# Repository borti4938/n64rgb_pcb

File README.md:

N64RGBv2.1 (PCB)
---

This repository contains all you need files to build your own DIY N64RGBv2.1 board.
Firmware is supplied in another repository.

Please don't ask me for selling a modding.
I either sell some prototypes on some forums marketplaces (which is very unlikely) or I don't have any of the boards.
This is a complete DIY modding project.
Everybody is on his own here.

**WARNING:**
This is an advanced DIY project if you do everything on your own. You need decent soldering skills.
The CPLD and the video DAC have 0.5mm fine pitched pins.
On the board there are some SMD1206 resistor and ferrite bead arrays.
However, there are some awesome shops out there selling the boards for a great price.

## Table of Contents

- [Checklist](https://github.com/borti4938/n64rgb_pcb#checklist-how-to-build-the-project)
- [Assembly](https://github.com/borti4938/n64rgb_pcb#assembly)
- [Installation](https://github.com/borti4938/n64rgb_pcb#installation)
  - [1. Open the Console](https://github.com/borti4938/n64rgb_pcb#1-open-the-console)
  - [2. Optional Steps](https://github.com/borti4938/n64rgb_pcb#2-optional-steps)
  - [3. Solder Work](https://github.com/borti4938/n64rgb_pcb#3-solder-work)
  - [4. Mount the N64 Advanced Modding PCB](https://github.com/borti4938/n64rgb_pcb#4-mount-the-n64-advanced-modding-pcb)
  - [5. Finish the Work](https://github.com/borti4938/n64rgb_pcb#5-finish-the-work)
- [Jumper Setup](https://github.com/borti4938/n64rgb_pcb#jumper-setup)
- [Cable Setup](https://github.com/borti4938/n64rgb_pcb#cable-setup)

## Checklist: How to build the project

- Use PCB files (either [KiCad-PCB design file](./n64rgbv2.1.kicad_pcb) or [Gerber files](./Gerber/)) to order your own PCB or simply use the [shared project(s) on OSHPark](https://oshpark.com/profiles/borti4938)
- If you paln to use solder paste, do not forget to order a stencil for top and bottom, too
- Source the components you need, e.g. from Mouser or Digikey.  
  The BOM is available in [here](./doc/BOM_n64rgbv2.1.xlsx).
- Wait for everything to arrive
- Assemble your PCB if you haven't use a PCBA service
- Set all jumpers
- Flash the firmware ([firmware releases](https://github.com/borti4938/n64rgb_fw/releases)) to the CPLD after installation (e.g. using an Altera USB Blaster)
  - Use the POF programming file named n64rgbv2\_1\__cpld-device_.pof
  - Using the intelFPGA programmer, JTAG chain is initialized by loading POF file
  - N64 needs to be powered for flashing
  - Power cycle the N64 after flashing
- If you want to go for a clean installation with custom made flexible PCBs, just visit the repository for add ons ([Flex PCB for the digital video interface](https://github.com/borti4938/n64rgb_project_misc/RCP2N64RGB), [Flex PCB for the analog video output](https://github.com/borti4938/n64rgb_project_misc/N64RGB2MoutFilter)

## Assembly

If you have all components available, you can start assembly your board.
The documentation provides assembly sheets ([top](./doc/n64rgb2.1_assembly_sheet_top.pdf) and [bottom](./doc/1_assembly_sheet_bot.pdf), which you can print out.
Together with the [BOM](./doc/BOM_n64rgbv2.1.xlsx) it is just a matter of time and effort to assembly everything.
Alternatively you can also use the [interactive BOM](./doc/ibom.html).

Please note that the assembly (and component sourcing) depends on which kind of CPLD family you use.
Supported are Max II and Max V CLPDs.
- If you use a Max II CPLD, you must use FB3 and leave U4, C41 and C42 unpopulated.
- If you use a Max V CPLD, you must use U4, C41 and C42 and leave FB3 unpopulated.

If you populate J3, which is the JTAG connector, please short the pins such that they are flush at the bottom side.
This reduces the risk to short on of these pins with the heat sink (where the PCB will be mounted).

Using non-clean flux (rosin based) is obviously recommended.
Even though it is "non-clean" I recommend cleaning everything afterwards (just for the visual finish).

Please double check everything for shorts once you finished your work.
Very important is that the power supply trace do not short to GND.
- 3.3V against GND (e.g. at C1 and at C52)
- 1.8V against GND (e.g. at C42)
- 5V against GND (e.g. at C4)

## Installation

Note that installation pictures partially show the N64Advanced board.
Pad design and installation is equivalent.

### 1. Open the console

- Remove Jumper Pak / Expansion Pak
- Remove screws from bottom side of the console  
(needs a 4.5mm gamebit tool)
- Lift top housing
- remove inner screws as marked  
(very last consoles made the heat sink design changed slightly)
- pull out the mainboard
- remove heat sink and RF shield
- **Hint** Now you have the chance to clean up your N64 shell

(image by Zerberus (circuit-board.de user))

### 2. Optional Steps

#### 2.1 Preparation of Top RF Shield

This step is optional.
It helps a) to reduce mechanical stress on the flex cable (if used) and b) ensures maximal distance between digital signals (installation wires or flex cable) and analog signals (MultiOut).

- Locate the tap in the RF shield next to the cartridge slot at the side of the MultiOut.  
(this is the place where the installation wires / flex cable will be routed through)
- option 1: bend the tap away

- option 2: simply cut the tab incl. the small piece up to the step in the RF shield

##### Some explanation on this optional step

Later, the data lines as well as the clock will be routed close to the MultiOut.
The distance between both is a crucial issue as your wires act as interferer.
Hence, having the tap bended might be ok, but it is better to cut some piece of the RF shield away to further increase the distance between MultiOut and data lines

#### GND insulation on the MultiOut

To have a better return path for the digital video lines defined, you may insulate GND from the MultiOut.
This step is only recommended if you have a noisy picture.
It comes with the drawback that a) you have a lot of more effort during installation and b) having a longer return path for the analog audio output as well as for S-Video and Composite Video as GND is later routed over the modding board.

- de-solder the MultiOut connector
- drill out the GND pads
- insulare the drills (e.g. with varnish (flex cable or wire install) or small shrink tubes (only wire installation))
- solder MultiOut back into place

### 3. Solder Work

You have the options to either install everything with casual installation wires or using flex cables.
This is just a trade-off between personal installation effort and price.
Personally, I recommend using the flex cable.

Sections 3.1 and 3.2 assume that you want to use the controller functions, so controller 1 will be connected.
However, this is optional, yet at the flex install the controller pad of the flex cable must not be left open!
Please also note section 3.3, where the installation of mechanical switches is described.

#### 3.1 Using the Flex Cable 

To use this option, you have to have the flex cables as shown at hand.
Note that the picture shows older prototype version.

##### 3.1.1 Digital inputs

Start with the digital side:
- Solder the RCP connector side to the RCP-NUS as shown
  - first pin bottom – 8
  - last pin to – 28
- Connect 3.3V to the flex, e.g. taken from C141
- Connect Ctrl. and reset
  - reset from PIF-NUS pin 27
  - Controller from PIF-NUS pin 16  
  (Make sure that PIF-NUS pin 16 is connected to the middle pin of controller port 1, otherwise search for a suitable connection point)
- bend the flex as marked in a way such that you do not see the shaded area anymore.  
The flex will be routed over the MultiOut.

**Note**: when using the flex of version earlier than _v2022xxyy_ you need to cut the RF shield near the MultiOut as shown in 2.1

##### 3.1.2 Analog outputs

Next up is the analog video flex which will be connected to the MultiOut.
Before you start here, make yourself clear where you want to route sync to.
This depends on whether you want to use sync on luma or sync on composite sync (raw sync) cable.

- Free the sync pin from the MultiOut, which means that you must trace back the copper track from the MultiOut pin and make sure that there is nothing connected to.
  - pin 3 (raw sync cable): usually unconnected. Only connected in earlier NTSC console (-CPU-01 to -CPU-03)
  - pin 7 (luma sync cable): usually connected. Search for a nearby resistor or trace back to the DENC-NUS or MAV-NUS and lift the luma pin. Remove the resistor or lift the pin at the DENC-NUS or MAV-NUS.
- solder the flex on its place of the MultiOut
- close **SJ1** on the flex from
  - middle to 3 if using raw sync
  - middle to 7 if using luma sync
- Note that it is also possible to connect sync pin 9 if you want to use a sync on composite video cable.
  - disconnect composite vide from pin 9 using the back tracing technique
  - solder a small wire from **SJ1** middle pad to pin 9 of the MultiOut

#### 3.2 Using Wires

First you need to work out the digital video signals as well as reset and controller 1. 
Most of the signals needed has to be taken from video processor output; the RCP-NUS.
Next to the RCP-NUS is the video encoder, where several types are used during the variety of N64 designs.
The pinouts are given below.
Basically, we need D0-D6, /DSYNC and /CLK (or VCLK or CLOCK) for the modding board.

(RCP-NUS picture by Marshall; Encoder picture by Viletim)

Next to the video signals, you will need to get power (3.3V and GND), reset and controller 1.
This means you need in total 13 wires.
If you use a ribbon cable, I recommend you to use either a 15 conductor cable (double 3.3V and GND) or a 11 conductor cable and separate 3.3V and GND wires. 

- Locate the video encoder
  - Solder a bunch of wires to the video signal pins D0-D6, /DSYNC and /CLK
- Solder wires for reset and controller 1
  - reset from PIF-NUS pin 27
  - Controller from PIF-NUS pin 16  
  (Make sure that PIF-NUS pin 16 is connected to the middle pin of controller port 1, otherwise search for a suitable connection point)
- Solder two additional wires for 3.3V (can be picked off C141) and one for GND (large GND plane)
- Route all wires to the MultiOut port

Next you can prepare wires for the analog video.
Connect several wires to the MultiOut.
Before you start here, make yourself clear where you want to route sync to.
This depends on whether you want to use a sync on composite video, a sync on luma or a sync on composite sync (raw sync) cable.

- Free the sync pin from the MultiOut, which means that you have to trace back the copper track from the MultiOut pin and make sure that there is nothing connected to.
  - pin 3 (raw sync cable): usually unconnected. Only connected in earlier NTSC console (-CPU-01 to -CPU-03)
  - pin 7 (luma sync cable): usually connected. Search for a nearby resistor or trace back to the DENC-NUS or MAV-NUS and lift the luma pin. Remove the resistor or lift the pin at the DENC-NUS or MAV-NUS.
  - pin 9 (composite video sync cable): usually connected. Search for a nearby resistor or trace back to the DENC-NUS or MAV-NUS and lift the luma pin. Remove the resistor or lift the pin at the DENC-NUS or MAV-NUS.
- Prepare some wires to the following pins
  - pin 1: red
  - pin 2: green
  - pin 4: blue
  - pin 3, 7 or 9: sync
  - pin 5 and/or 6: GND (connect pin 5 **and** pin 6 if you insulated GND from the MultiOut)
  - pin 10: 5V

You have the option to use the [Filter AddOn board](https://github.com/borti4938/n64rgb_project_misc/tree/master/FilterAddOn) here.
Note that the filter is optionally included in on the flex cable setup.

If you use the filter board, you clearly have to solder the filter board first and connect the wire to the pads of the filter board as marked on the silk screen.

#### 3.3 Mechanical switch

You can install mechanical switches to toggle VI-DeBlur on and off and also 16bit mode on and off.
At least I recommend installing a mechanical switch for the VI-DeBlur function.

Source a on/on or on/off switch like [this one](https://etim.net.au/shop/shop.php?crn=209&rn=559&action=show_detail).
If you source the switch as linked you can use [this 3D mount](https://www.thingiverse.com/thing:4584239) for a clean installation.

Connect the switch to J11.1 (VI-DeBlur) and/or to J11.2 (16bit mode) in a way such that the switch leaves the jumper open in one position and closes it at the other position.

### 4. Mount the N64 Advanced Modding PCB

The PCB is designed to fit on the heat sink of the N64.
There is a large via on the PCB where a M3 screw passes through.
Mount the PCB using a M3 screw of length 10mm or 12mm, a set of washers and a nut.
Be careful with the JTAG connector **J3** and ensure that the pins do not short to the heatsink!

If you want to use the heat sink shield as an additional secure GND connection, you can also apply some solder to the mounting via.

If everything is mounted and secured, the PCB should sit like that.

### 5. Finish the Work

Before continuing you can assemble the RF shield and heat sink back to the N64 mainboard.
In that way everything is secured in place where it belongs to.
Of course, if you use an installation with wires, make sure that you know which wire is for what.
On my ealrier installs I used some wire marker.

#### 5.1 With Flex Cable

Bend the flex cables gently at the shaded areas.
In that way you should be able to allign both flex cables at the N64RGBv2.1 modding board.
Solder the flex cables at their places.
(Please note subsection 5.3 - CSYNC).

Connect an extra GND wire as shown in 5.3.

#### 5.2 With Wires

Just connect every wire at its place.
The silk screen shows you where everything goes to.
(Please note subsection 5.3 - CSYNC).
Note that the picture shows an older version of the N64 Advanced.
Newer versions have reset and controller at the left-hand side.

Connect an extra GND wire as shown in 5.4.

#### 5.3 CSYNC

You have the option to connect _/CS_ or _/CS (75ohm)_.
I recommend using _/CS (75ohm)_ except if you have a true TTL sink, which is usually not the case!
In virtually 99% of all setups connecting the sync wire to _/CS (75ohm)_ is the way to go.

On installations with the flex cables follows that you must close SJ3 bottom on the flex.
Please note the Jumper Setup section to correctly setup the sync level.

#### 5.4 Extra GND Wire

Connect an extra GND wire to the heat sink screw.
This improves return path properties of the digital video lines.

## Jumper Setup

Jumpers with three pads have _J1#.1_ and _J1#.2_, where .1 is marked with an _arrow_.
Closing either jumper means that a short to the middle pad is needed.

#### J11 (VI-DeBlur and 16bit mode)

This jumper can act as a power cycle default.
You can also switch the state of the jumper using a mechanical switch to toggle the functions during runtime.

##### J11.1 
- opened: VI-DeBlur off
- closed: VI-DeBlur on

##### J11.2
- opened: 16bit mode off
- closed: 16bit mode on

#### J12 (IGR function control)
##### J12.1 (VI-DeBlur and 16bit mode)
- opened: controller functions for toggle VI-DeBlur and 16bit mode on/off are enabled
- closed: controller functions are disabled

##### J12.2 (in game reset)
- opened: reset by controller enabled
- closed: reset by controller disabled

#### J2 (Filter setup)
Needs filter add on to be installed.

- opened: use low pass filter
- closed: bypass filter

#### J21 (Sync on Green)
- open: SoG disabled
- closed: SoG enabled

#### J31 (CSYNC level @ _/CS (75ohm)_ pad)

- opened: appr. 1.87V @ 75ohm termination, i.e. needs a resistor inside the sync wire further attenuating the signal. Designed to work for cables with 470 ohm resistor inside resulting in appr. 450mV @ 75ohm termination
- closed: appr. 300mV @ 75ohm termination suitable for pass through wired cables at sync, works with standard TV / scaler setup

#### J3
_J3_ is the JTAG connector.

## Cable Setup

| Signal | Pin MultiOut | Pin SCART | Ref. GND in SCART | Cinch Plug | Note |
|:-------|:-------------|:----------|:------------------|:-----------|:-----|
| Red / Pr | 1 | 15 | 13 | Red plug | Using a 220uF cap in series is possible, yet not required |
| Green / Y | 2 | 11 | 9 | Green plug | Using a 220uF cap in series is possible, yet not required |
| Blue / Pb | 4 | 7 | 5 | Blue plug | Using a 220uF cap in series is possible, yet not required |
| Sync | 3, 7 or 9 | 20 | 17 | _not needed_ | Pin: See installation, Cable: see notes below |
| GND | 5, 6 | 4,5,9,13,17,18,21 | | Outer ring of each plug | Pin 21 @ SCART: outer shield |
| +5V | 10 | 16 | 18 | _not needed_ | SCART: use a 180ohm resistor in series |
| Audio left | 11 | 6 | 4 | Red plug | |
| Audio right | 12 | 2 | 4 | White plug | |

#### Notes on Sync:

- I recommend using the 75ohm compatible csync output.  
  You have a modding board with J31, you can select with J31 whether
  - you have a series resistor in you cable (J31 open) or
  - if you have a straightly wired sync connection (J31 closed).
- If you use TTL sync output, you have to add an additional resistor in series in every case if you want to use the cable on a non-TTL setup (0ohm to 900ohm) to attenuate the signal for  sinks with 75ohm.

#### RGB cables:

- If you buy an RGB cable, buy a typical RGB cable for a NTSC SNES with sync on luma (MultiAV pin 7) or sync on csync (MultiAV pin 3).
- If you bought a raw csync cable and if you use the 75ohm output, please ensure to set J31 correctly
  
#### PAL RGB cables (SNES PAL):

- PAL RGB cable, i.e. a cable with additional 75ohm resistors to GND, are not supported out of the box.
- You can support them if and only if you have the _Filter AddOn_.  
  To support the cable, replace RN2 with a 39ohm resistor array or solder a second 75ohm resistor array on top of the existing one.

#### RGsB Cables (Cinch):

With the given table you should be able to build your own component cable (passing RGB) or to build an adapter (see pictures below)
Unfortunately, there are no cables / adapter to buy.
Only chance is to buy a Wii component cable and use a MultiOut adapter (SNES/N64/GC style to Wii style).

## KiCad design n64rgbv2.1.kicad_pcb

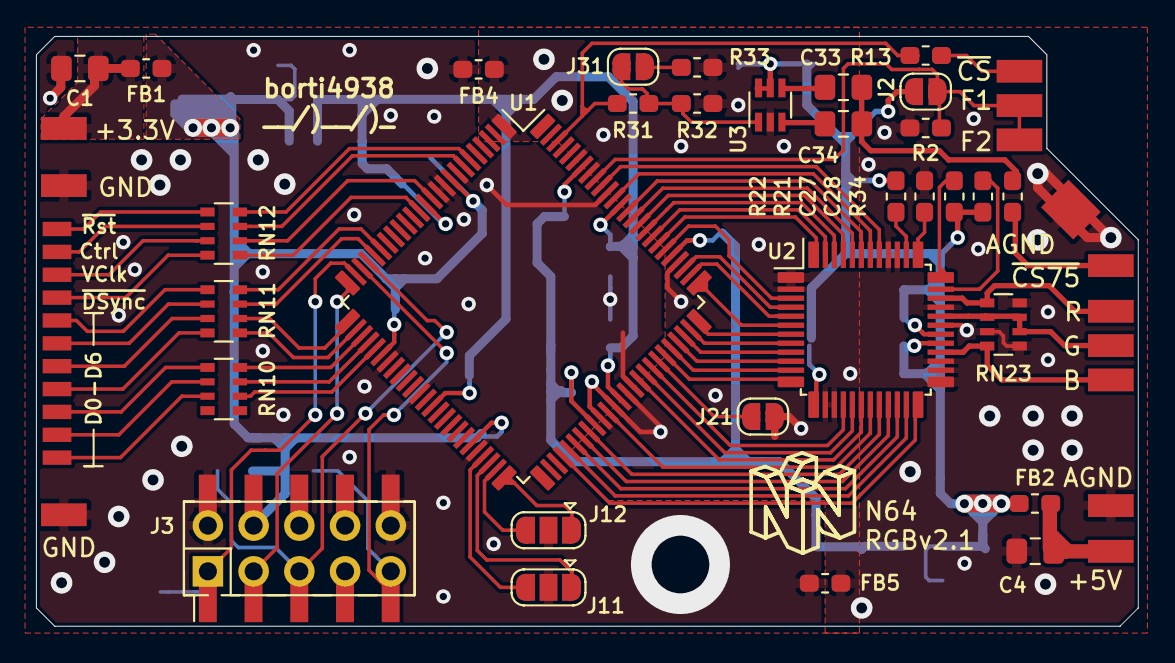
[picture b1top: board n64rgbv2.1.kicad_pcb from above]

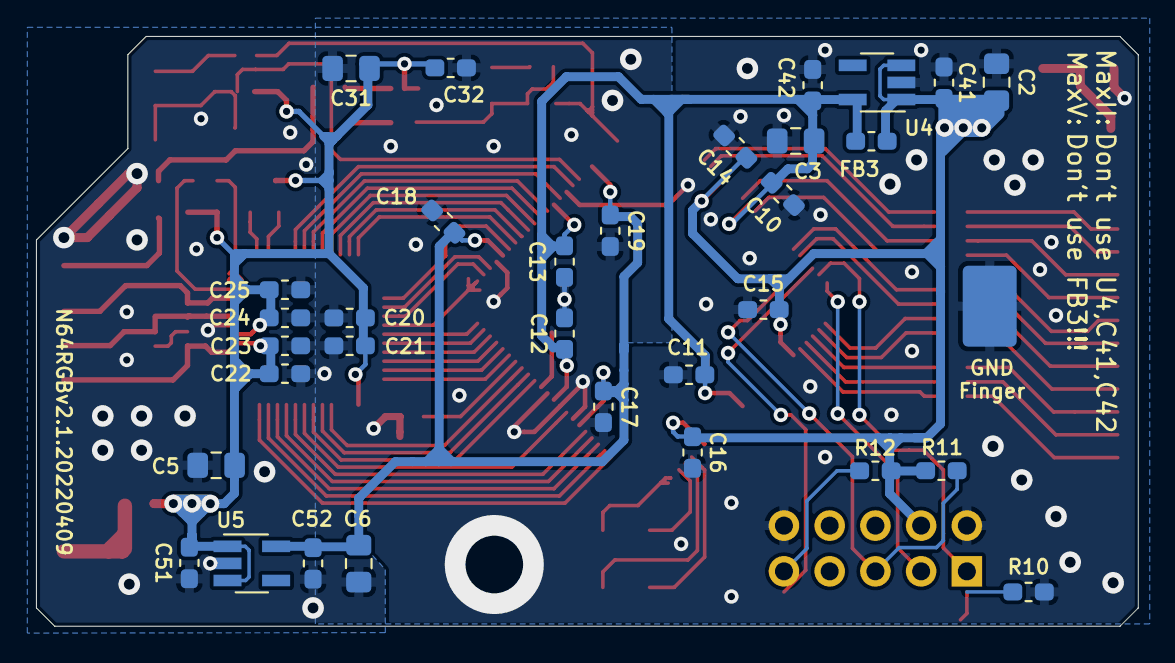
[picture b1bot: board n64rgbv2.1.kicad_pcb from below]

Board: 2 copper layers, 61.2 x 32.8 mm, 90 parts (33 on the bottom side), 82 nets.

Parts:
C1, C4: 47u; C_0805_2012Metric_Pad1.15x1.40mm_HandSolder
C2, C3, C5, C6, C31: 10u; C_0805_2012Metric_Pad1.15x1.40mm_HandSolder
C10, C11, C12, C13, C14, C15, C16, C17, C18, C19, C20, C22, C24, C27, C28: 0.1u; C_0603_1608Metric_Pad1.05x0.95mm_HandSolder
C21, C23, C25, C32: 0.01u; C_0603_1608Metric_Pad1.05x0.95mm_HandSolder
C33: 33u; C_0805_2012Metric_Pad1.15x1.40mm_HandSolder
C34: 22u; C_0805_2012Metric_Pad1.15x1.40mm_HandSolder
C41, C42, C51, C52: 1u; C_0603_1608Metric_Pad1.05x0.95mm_HandSolder
FB1, FB2, FB3, FB4, FB5: MPZ1608S221ATA00; R_0603_1608Metric_Pad1.05x0.95mm_HandSolder
J2, J21, J31: SolderJumper_2_Open; SolderJumper-2_P1.3mm_Open_RoundedPad1.0x1.5mm
J3: 30310-6002HB; PinHeader_2x05_P2.54mm_Vertical
J3b1: 30310-6002HB; PinHeader_2x05_P2.54mm_Vertical_SMD
J11, J12: SolderJumper_3_Open; SolderJumper-3_P1.3mm_Open_RoundedPad1.0x1.5mm
P_3V3, P_5V1: Conn_01x01; Wirepad_1.27_2.54
P_B1: Conn_01x01; Wirepad_1.27_2.54
P_CS1: Conn_01x01; Wirepad_1.27_2.54
P_CS_75: Conn_01x01; Wirepad_1.27_2.54
P_CTRL1: Conn_01x01; Wirepad_0.8_1.6
P_D0, P_D1, P_D2, P_D3, P_D4, P_D5, P_D6: Conn_01x01; Wirepad_0.8_1.6
P_DSYNC1: Conn_01x01; Wirepad_0.8_1.6
P_F1, P_F2: Conn_01x01; Wirepad_1.27_2.54
P_G1: Conn_01x01; Wirepad_1.27_2.54
P_GND_0, P_GND_1, P_GND_2, P_GND_3, P_GND_4: Conn_01x01; Wirepad_1.27_2.54
P_R1: Conn_01x01; Wirepad_1.27_2.54
P_RST1: Conn_01x01; Wirepad_0.8_1.6
P_VCLK1: Conn_01x01; Wirepad_0.8_1.6
R2, R11, R12: 10k; R_0603_1608Metric_Pad1.05x0.95mm_HandSolder
R10: 1k; R_0603_1608Metric_Pad1.05x0.95mm_HandSolder
R13: 330; R_0603_1608Metric_Pad1.05x0.95mm_HandSolder
R21: 518/515; R_0603_1608Metric_Pad1.05x0.95mm_HandSolder
R22, R31: 4k7; R_0603_1608Metric_Pad1.05x0.95mm_HandSolder
R32: 6k19; R_0603_1608Metric_Pad1.05x0.95mm_HandSolder
R33: 523; R_0603_1608Metric_Pad1.05x0.95mm_HandSolder
R34: 75; R_0603_1608Metric_Pad1.05x0.95mm_HandSolder
RN10, RN11, RN12: CAT16-47R0F4LF / CAY16-47R0F4LF; R_Array_Convex_4x0603
RN23: CAY16-75R0F4LF; R_Array_Convex_4x0603
SHIELD_FINGER1: S1761-42R; Pad_4.5_3.0
U1: EPM570T100; TQFP-100_14x14mm_P0.5mm
U2: ADV7125; LQFP-48_7x7mm_P0.5mm
U3: TSH122ICT; SC-70-6
U4: TLV70018_SOT23-5; SOT-23-5_HandSoldering
U5: TLV70033_SOT23-5; SOT-23-5_HandSoldering

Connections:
+1V8: C3.1, C10.1, C11.1, C12.1, C13.1, C42.1, FB3.1, U1.13 (VCCINT), U1.39 (VCCINT), U1.63 (VCCINT), U1.88 (VCCINT), U4.5 (OUT)
+3.3VADC: C2.1, C14.1, C15.1, C16.1, C41.1, FB1.1, FB3.2, J3.4, J3b1.4, R11.1, R12.1, U1.9 (VCCIO1), U1.31 (VCCIO1), U1.45 (VCCIO1), U4.1 (IN), U4.3 (EN)
+3V3: C6.1, C17.1, C18.1, C19.1, C52.1, U1.59 (VCCIO2), U1.80 (VCCIO2), U1.94 (VCCIO2), U5.5 (OUT)
+5VA: C5.1, C20.1, C21.1, C22.1, C23.1, C24.1, C25.1, C27.2, C28.2, C31.1, C32.1, C51.1, FB2.1, J2.1 (A), R22.1, U2.13 (VAA), U2.29 (VAA), U2.30 (VAA), U3.5 (EN), U3.6 (Vcc), U5.1 (IN), U5.3 (EN)
/B0: U1.68 (IO2_68), U2.16 (B0)
/B1: U1.67 (IO2_67), U2.17 (B1)
/B2: U1.66 (IO2_66), U2.18 (B2)
/B3: U1.61 (IO2_61), U2.19 (B3)
/B4: U1.58 (IO2_58), U2.20 (B4)
/B5: U1.57 (IO2_57), U2.21 (B5)
/B6: U1.56 (IO2_56), U2.22 (B6)
/B7: U1.55 (IO2_55), U2.23 (B7)
/CTRL_cpld: RN12.7 (R2.2), U1.7 (IO1_7)
/D0_cpld: RN10.6 (R3.2), U1.30 (IO1_30)
/D1_cpld: RN10.7 (R2.2), U1.29 (IO1_29)
/D2_cpld: RN10.8 (R1.2), U1.28 (IO1_28)
/D3_cpld: RN11.5 (R4.2), U1.27 (IO1_27)
/D4_cpld: RN11.6 (R3.2), U1.26 (IO1_26)
/D5_cpld: RN11.7 (R2.2), U1.21 (IO1_21)
/D6_cpld: RN11.8 (R1.2), U1.20 (IO1_20)
/DSYNC_cpld: RN12.5 (R4.2), U1.14 (IO1_14/GCLK1)
/G0: U1.81 (IO2_81), U2.3 (G0)
/G1: U1.78 (IO2_78), U2.4 (G1)
/G2: U1.77 (IO2_77), U2.5 (G2)
/G3: U1.76 (IO2_76), U2.6 (G3)
/G4: U1.75 (IO2_75), U2.7 (G4)
/G5: U1.74 (IO2_74), U2.8 (G5)
/G6: U1.73 (IO2_73), U2.9 (G6)
/G7: U1.72 (IO2_72), U2.10 (G7)
/R0: U1.91 (IO2_91), U2.41 (R0)
/R1: U1.89 (IO2_89), U2.42 (R1)
/R2: U1.87 (IO2_87), U2.43 (R2)
/R3: U1.86 (IO2_86), U2.44 (R3)
/R4: U1.85 (IO2_85), U2.45 (R4)
/R5: U1.84 (IO2_84), U2.46 (R5)
/R6: U1.83 (IO2_83), U2.47 (R6)
/R7: U1.82 (IO2_82), U2.48 (R7)
/RST_cpld: RN12.8 (R1.2), U1.6 (IO1_6)
/VCLK_ADV: U1.54 (IO2_54), U2.24 (VCLK)
/VCLK_cpld: RN12.6 (R3.2), U1.12 (IO1_12/GCLK0)
/VIDeBlur_t: J11.1 (A), U1.48 (IO1_48)
/en_IGR_DeBl_15b_Func: J12.1 (A), U1.50 (IO1_50)
/en_IGR_Rst_Func: J12.3 (B), U1.49 (IO1_49)
/~15b_mode_t: J11.3 (B), U1.47 (IO1_47)
/~BLANK: U1.71 (IO2_71), U2.11 (#BLANK)
/~CSYNC_75_pre: J31.1 (A), R31.2, R32.1, U3.1 (IN)
/~CSYNC: R13.2, R31.1, U1.98 (IO2_98)
/~SYNC: U1.70 (IO2_70), U2.12 (#SYNC)
/~SoG: J21.1 (A), U1.69 (IO2_69)
B_o: P_B1.1, RN23.4 (R4.1), U2.28 (IOB)
CTRL_i: P_CTRL1.1, RN12.2 (R2.1)
D0_i: P_D0.1, RN10.3 (R3.1)
D1_i: P_D1.1, RN10.2 (R2.1)
D2_i: P_D2.1, RN10.1 (R1.1)
D3_i: P_D3.1, RN11.4 (R4.1)
D4_i: P_D4.1, RN11.3 (R3.1)
D5_i: P_D5.1, RN11.2 (R2.1)
D6_i: P_D6.1, RN11.1 (R1.1)
DSYNC_i: P_DSYNC1.1, RN12.4 (R4.1)
Filter_Bypass: J2.2 (B), P_F1.1, P_F2.1, R2.1, U1.92 (IO2_92)
GND: C4.2, C5.2, C6.2, C17.2, C18.2, C19.2, C20.2, C21.2, C22.2, C23.2, C24.2, C25.2, C31.2, C32.2, C51.2, C52.2, FB4.1, FB5.1, J21.2 (B), P_GND_2.1, P_GND_3.1, P_GND_4.1, R2.2, R21.2, R32.2, R33.2, RN23.3 (R3.1), RN23.5 (R4.2), RN23.8 (R1.2), U1.1 (IO2_1), U1.60 (GNDIO), U1.62 (IO2_62/GCLK2), U1.64 (IO2_64/GCLK3), U1.79 (GNDIO), U1.93 (GNDIO), U1.95 (IO2_95), U2.1 (GND), U2.2 (GND), U2.14 (GND), U2.15 (GND), U2.25 (GND), U2.26 (GND), U2.27 (#IOB), U2.31 (#IOG), U2.33 (#IOR), U2.39 (GND), U2.40 (GND), U3.2 (GND), U5.2 (GND)
GNDD: C1.2, C2.2, C3.2, C10.2, C11.2, C12.2, C13.2, C14.2, C15.2, C16.2, C41.2, C42.2, FB4.2, FB5.2, J3.2, J3.10, J3b1.2, J3b1.10, J11.2 (C), J12.2 (C), P_GND_0.1, P_GND_1.1, R10.1, SHIELD_FINGER1.1, U1.8 (IO1_8), U1.10 (GNDIO), U1.11 (GNDINT), U1.32 (GNDIO), U1.37 (GNDINT), U1.46 (GNDIO), U1.65 (GNDINT), U1.90 (GNDINT), U4.2 (GND)
G_o: P_G1.1, RN23.2 (R2.1), RN23.6 (R3.2), RN23.7 (R2.2), U2.32 (IOG)
unnamed: C1.1, FB1.2, P_3V3.1
unnamed: C4.1, FB2.2, P_5V1.1
unnamed: C27.1, U2.36 (VREF)
unnamed: C28.1, U2.35 (COMP)
unnamed: J31.2 (B), R33.1
unnamed: R21.1, U2.37 (RSET)
unnamed: R22.2, U2.38 (#PSAVE)
unnamed: C33.2, C34.2, R34.2
unnamed: C34.1, U3.3 (SAG)
unnamed: C33.1, U3.4 (OUT)
RST_io: P_RST1.1, RN12.1 (R1.1)
R_o: P_R1.1, RN23.1 (R1.1), U2.34 (IOR)
TCK: J3.1, J3b1.1, R10.2, U1.24 (TCK)
TDI: J3.9, J3b1.9, R12.2, U1.23 (TDI)
TDO: J3.3, J3b1.3, U1.25 (TDO)
TMS: J3.5, J3b1.5, R11.2, U1.22 (TMS)
VCLK_i: P_VCLK1.1, RN12.3 (R3.1)
~CSYNC_75_o: P_CS_75.1, R34.1
~CSYNC_LVTTL_o: P_CS1.1, R13.1

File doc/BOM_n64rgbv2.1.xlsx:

Number of PCBs |  | 3
Designator | MPN | QTY/PCB | QTY | DESCRIPTION | VALUE | PACKAGE | NOTES
ICs and Regulators
U1 | 5M570ZT100C5N | 1 | 3 | CPLD with 570LEs |  | TQFP100
 | 5M240ZT100C5N |  |  | CPLD with 240LEs |  | TQFP100 | Alternative to 5M570ZT100 with less LEs, leave J1 open
U2 | ADV7125KSTZ50 | 1 | 3 | Video DAC 8bit, 3Ch. |  | 48-LQFP | can be replaced with ADV7123KSTZ50 on demand
U3 | TSH122ICT | 1 | 3 | Video buffer |  | SC-70-6
U4 | TLV70018DDCR | 1 | 3 | 1.8V LDO regulator |  | SOT-23-5
U5 | TLV70033DDCR | 1 | 3 | 3.3V LDO regulator |  | SOT-23-5
Power Supply Filtering
C1,C4 |  | 2 | 6 | Ceramic capacitor, X5R | 47uF / 6.3V | SMD0805
FB1,FB2,FB4,FB5 | BLM18PG471SN1D | 4 | 12 | Ferrit bead |  | SMD0603
Remaining passive components
C2,C3,C5,C6,C31 |  | 5 | 15 | Ceramic capacitor, X5R | 10uF / 6.3V | SMD0805
C10-C19,C20,C22,C24,C27,C28 |  | 15 | 45 | Ceramic capacitor, X7R | 0.1uF / 50V (10%) | SMD0603
C21,C23,C25,C32 |  | 4 | 12 | Ceramic capacitor, X7R | 0.01uF / 50V | SMD0603
C33 |  | 1 | 3 | Ceramic capacitor, X5R | 33uF / 6.3V | SMD0805
C34 |  | 1 | 3 | Ceramic capacitor, X5R | 22uF / 6.3V | SMD0805
C41,C42,C51,C52 |  | 4 | 12 | Ceramic capacitor, X5R | 1uF / 6.3V | SMD0603
R10 | CRCW06031K00FKTB | 1 | 3 | Resistor | 1kohm (1%) | SMD0603
R2,R11, R12 | CRCW0603-10K | 3 | 9 | Resistor | 10kohm (1%) | SMD0603
R13 | RC0603FR-07330RL | 1 | 3 | Resistor | 330ohm (1%) | SMD0603
R21 | RC0603FR-07523RL | 1 | 3 | Resistor | 518 | SMD0603 | with ADV7123: use 516ohm resistor; for PAL-Standard: 528ohm/527ohm
 |  |  |  |  |  |  | Value of MPN reference differs to ideal value to allow for negative margin!
R22,R31 | RC0603FR-074K7L | 2 | 6 | Resistor | 4.7kohm (1%) | SMD0603
R32 | RC0603FR-076K19L | 1 | 3 | Resistor | 6.19kohm (1%) | SMD0603
R33 | RC0603FR-07523RL | 1 | 3 | Resistor | 523 | SMD0603 | usually same as R21
R34 | RC0603FR-0775RL | 1 | 3 | Resistor | 75 | SMD0603
RN10,RN11,RN12 | CAT16-47R0F4LF / CAY16-47R0F4LF | 3 | 9 | Resistor Array (4x) | 47 | SMD1206 | Use this if you don't have resistors at the RCP output or if you use a flex wit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
 | BK32164M121-T |  |  | Ferrite Beads MULTILYR CHP | BD 120OHMS 25% | SMD1206 | Use this alternative if you have resistors at the RCP output, e.g. with the "ol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
RN23 | CAT16-75R0F4LF / CAY16-75R0F4LF |  | 1 | Resistor Array (4x) | 75 | SMD1206
J3 | 3020-10-0300-00 | 1 | 3 | SMD part |  |  | JTAG Connector
 | 30310-6002HB |  |  | THT part alternative |  |  | JTAG Connector
Unpopulated Footprints
FB3 | Don't use FB3 in MaxV setup!!! Otherwise you'll harm your CPLD at first power c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
MPNs are only suggestions! You can use equivalent components, too.

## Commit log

2022-03-27 add readme
2022-03-27 add table of contents and a remark on MaxII and MaxV assembly differences
2022-03-29 remove some typos, adapt some wording
2022-07-13 typo fix
2022-07-13 misc updates: - update KiCad to v6 - add SMD footprint for JTAG connector
